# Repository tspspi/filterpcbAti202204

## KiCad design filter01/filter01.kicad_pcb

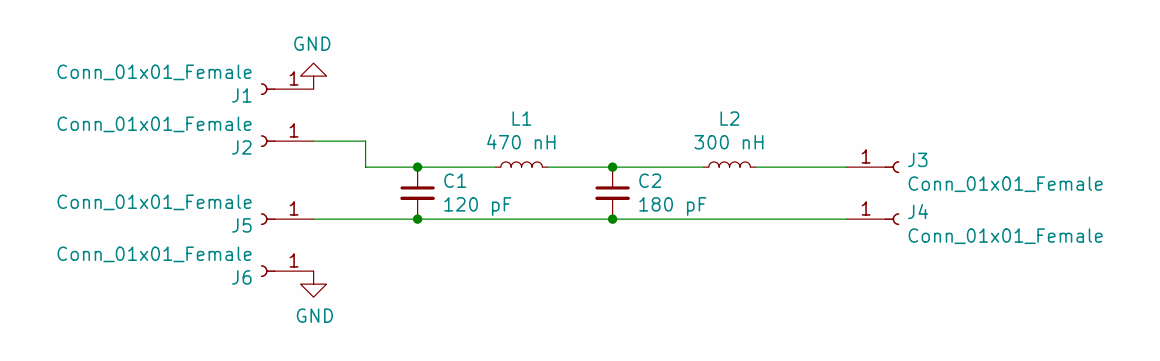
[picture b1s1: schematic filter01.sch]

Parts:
C1: 120 pF; C_0402_1005Metric
C2: 180 pF; C_1206_3216Metric
J1, J2, J5, J6: Conn_01x01_Female; SolderWirePad_1x01_SMD_1x2mm
J3, J4: Conn_01x01_Female; Pin_D1.0mm_L10.0mm_LooseFit
L1: 470 nH; L_1008_2520Metric
L2: 300 nH; L_1008_2520Metric

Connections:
GND: J1.1, J6.1
unnamed: C1.1, J2.1, L1.1
unnamed: C1.2, C2.2, J4.1, J5.1
unnamed: C2.1, L1.2, L2.1
unnamed: J3.1, L2.2

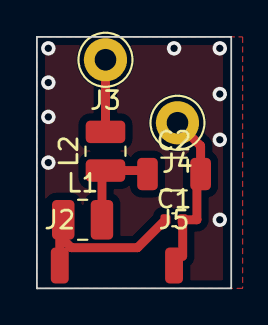
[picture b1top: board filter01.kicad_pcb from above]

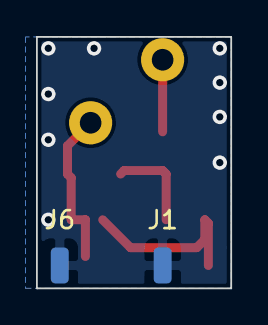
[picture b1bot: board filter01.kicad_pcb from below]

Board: 2 copper layers, 10.8 x 14.0 mm, 10 parts (2 on the bottom side), 5 nets.

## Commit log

2022-04-07 Final revision
2022-04-07 Generated gerber
2022-04-29 Removed old gerber output
2022-04-29 Updated gerber
2022-04-29 Fixed issued
